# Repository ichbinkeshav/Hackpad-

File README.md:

# HACKPAD+
<br>
This is a hackpad that is based on Xiao Rp2040 that has 9 Buttons and 2 Rotor encoder . I utilized the 2 buttons of rotor encoder as well. So in total i have 11 Keys and 2 rotor encoder. For Keys i used 3 x 4 Matrix so i just need 7 gpio pins for it and 4 gpios for 2 encoder. So the rotor encoder is used to control volume and brightness and the 11 keys are used for general useful shortcuts like copy ,paste ,delete ,screenshot ,open youtube ,cut ,undo ,redo ,print ,window close and open file explore, I did the Schematic and PCB on KICAD and 3d Design on Fusion. The Code is written in circuit Python and uses KMK.I used the hackclub guide , which really helped me a lot.<br>
##  Bill of Materials (BOM)

**#**
1 x XIAO RP2040<br>
**#**
9 x MX-Style switches <br>
**#**
9 x Blank DSA keycaps<br>
**#**
2 x EC11 Rotary Encoder<br>
**#**
4 x  M3x16mm screws <br>
**#**
4 x  M3x5mx4mm heatset inserts

**Schematic**<br><br>
<br><br>
**PCB**<br>
<br><br>
<br>
**Case**<br><br>

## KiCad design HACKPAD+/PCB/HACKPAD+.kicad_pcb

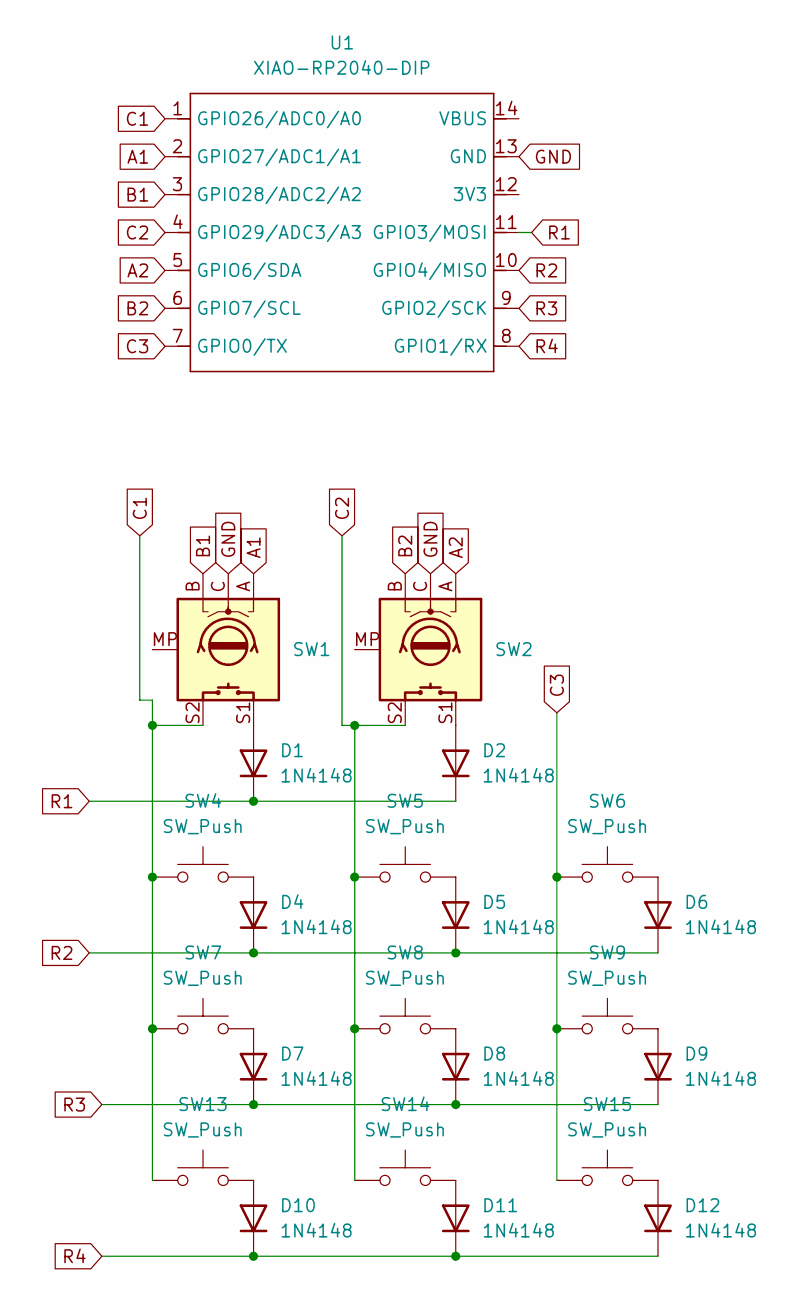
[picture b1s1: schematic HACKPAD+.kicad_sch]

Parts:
D1, D2, D4, D5, D6, D7, D8, D9, D10, D11, D12: 1N4148; D_DO-35_SOD27_P7.62mm_Horizontal
SW1, SW2: RotaryEncoder_Switch_MP; RotaryEncoder_Alps_EC11E-Switch_Vertical_H20mm
SW4, SW5, SW6, SW7, SW8, SW9, SW13, SW14, SW15: SW_Push; SW_Cherry_MX_1.00u_PCB
U1: XIAO-RP2040-DIP

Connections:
A1: SW1.A, U1.2 (GPIO27/ADC1/A1)
A2: SW2.A, U1.5 (GPIO6/SDA)
B1: SW1.B, U1.3 (GPIO28/ADC2/A2)
B2: SW2.B, U1.6 (GPIO7/SCL)
C1: SW1.S2, SW4.1, SW7.1, SW13.1, U1.1 (GPIO26/ADC0/A0)
C2: SW2.S2, SW5.1, SW8.1, SW14.1, U1.4 (GPIO29/ADC3/A3)
C3: SW6.1, SW9.1, SW15.1, U1.7 (GPIO0/TX)
GND: SW1.C, SW2.C, U1.13 (GND)
unnamed: D1.2 (A), SW1.S1
unnamed: D2.2 (A), SW2.S1
unnamed: D4.2 (A), SW4.2
unnamed: D5.2 (A), SW5.2
unnamed: D6.2 (A), SW6.2
unnamed: D7.2 (A), SW7.2
unnamed: D8.2 (A), SW8.2
unnamed: D9.2 (A), SW9.2
unnamed: D10.2 (A), SW13.2
unnamed: D11.2 (A), SW14.2
unnamed: D12.2 (A), SW15.2
R1: D1.1 (K), D2.1 (K), U1.11 (GPIO3/MOSI)
R2: D4.1 (K), D5.1 (K), D6.1 (K), U1.10 (GPIO4/MISO)
R3: D7.1 (K), D8.1 (K), D9.1 (K), U1.9 (GPIO2/SCK)
R4: D10.1 (K), D11.1 (K), D12.1 (K), U1.8 (GPIO1/RX)

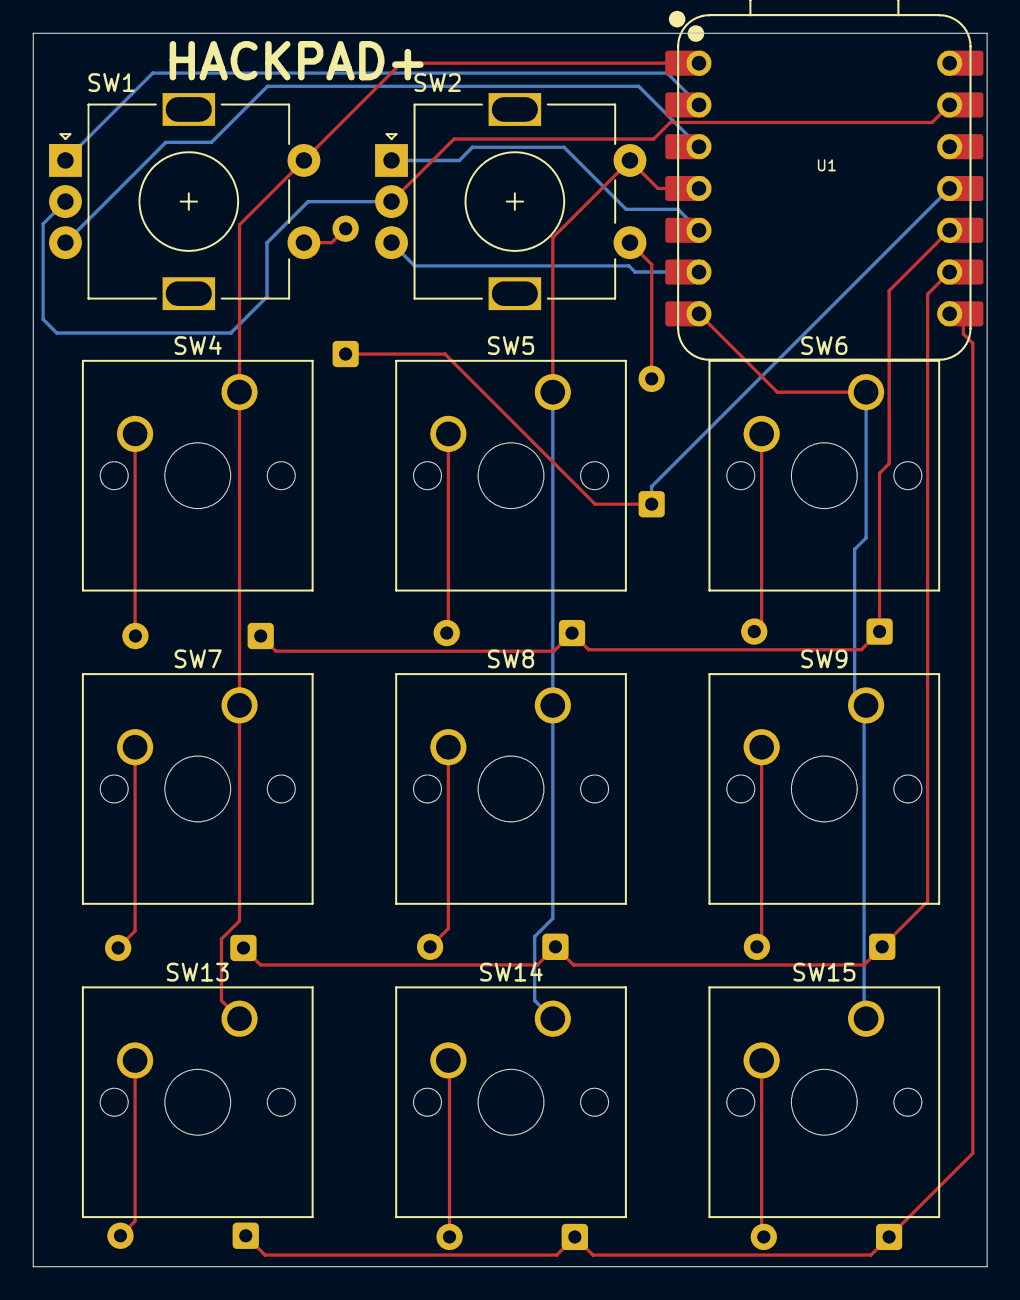
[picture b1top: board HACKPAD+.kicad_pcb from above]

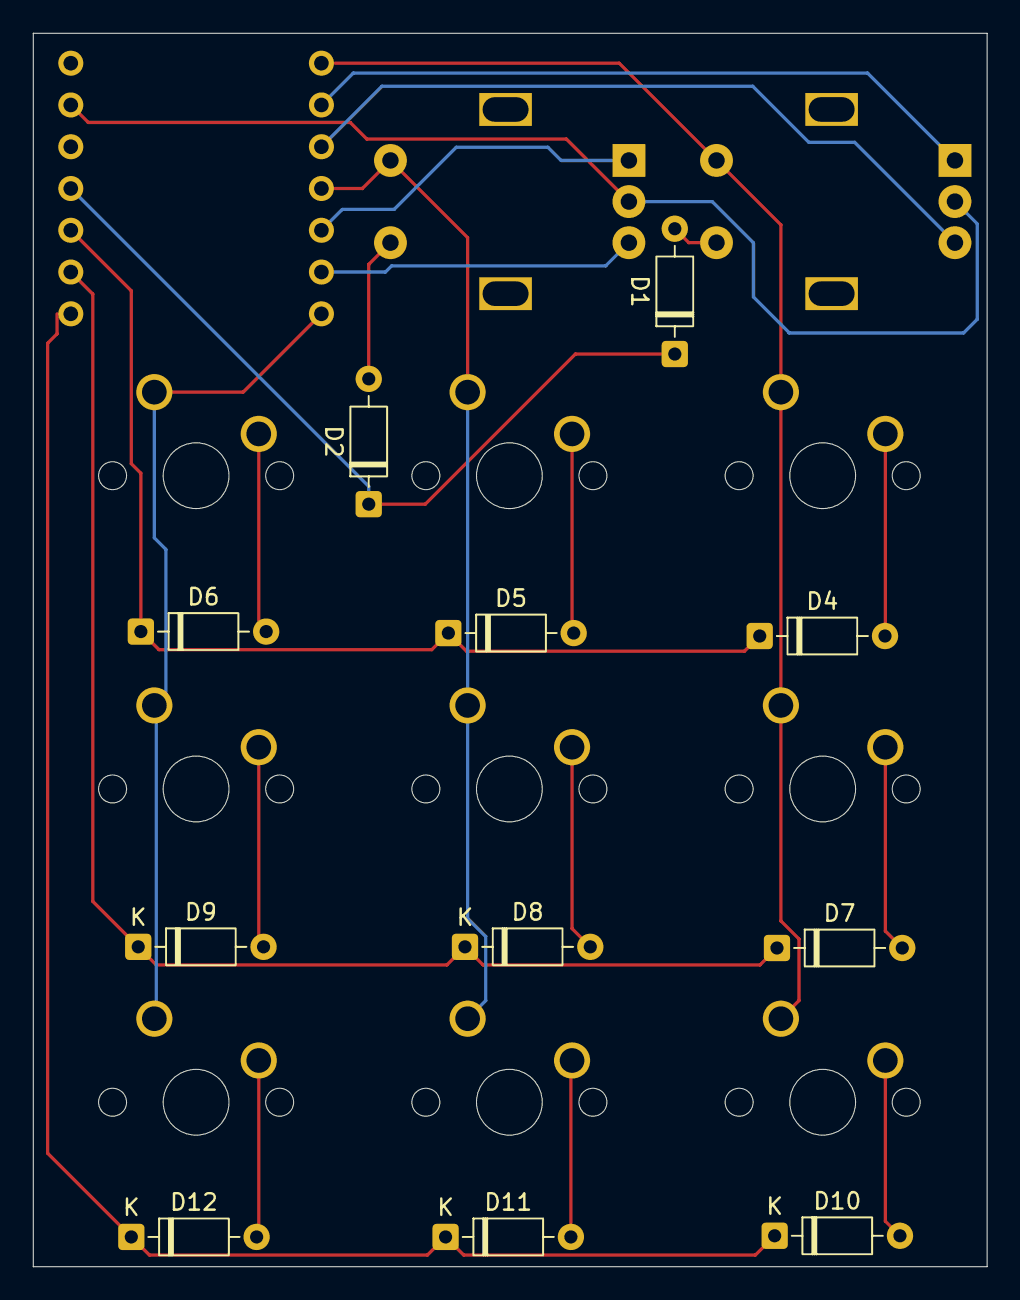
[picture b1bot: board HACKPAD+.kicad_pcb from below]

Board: 2 copper layers, 58.0 x 75.0 mm, 23 parts (11 on the bottom side), 23 nets.
